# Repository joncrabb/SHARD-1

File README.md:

# SHARD-1
Code for the Surrey High Altitude Radiation Detector (SHARD-1)

Code written for 2 Arduino Nano controllers. 

To be used as payload with the Surrey EARS (Electronics and Amateur Radio Society) High Altitude Balloon Project

Go here to the EARS repositoryy containing PCB designs and code for the OBC: https://github.com/SurreyEARS/EARS-HAB

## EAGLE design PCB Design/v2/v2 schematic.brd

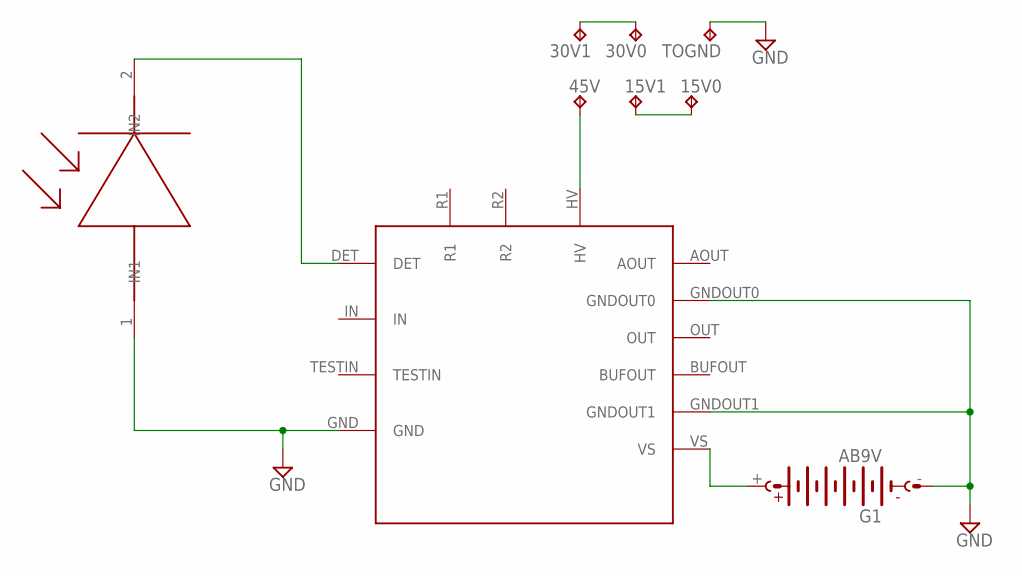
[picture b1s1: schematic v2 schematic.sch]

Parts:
15V0, 15V1, 30V0, 30V1, 45V: TP-063
G1: AB9V
PC21: A111
PINDIODE: S3590-08
TOGND: TP-063

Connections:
GND: G1.-, PC21.GND, PC21.GNDOUT0, PC21.GNDOUT1, PINDIODE.1 (IN1), TOGND.1
unnamed: 45V.1, PC21.HV
unnamed: 30V0.1, 30V1.1
unnamed: 15V0.1, 15V1.1
unnamed: G1.+, PC21.VS
unnamed: PC21.DET, PINDIODE.2 (IN2)

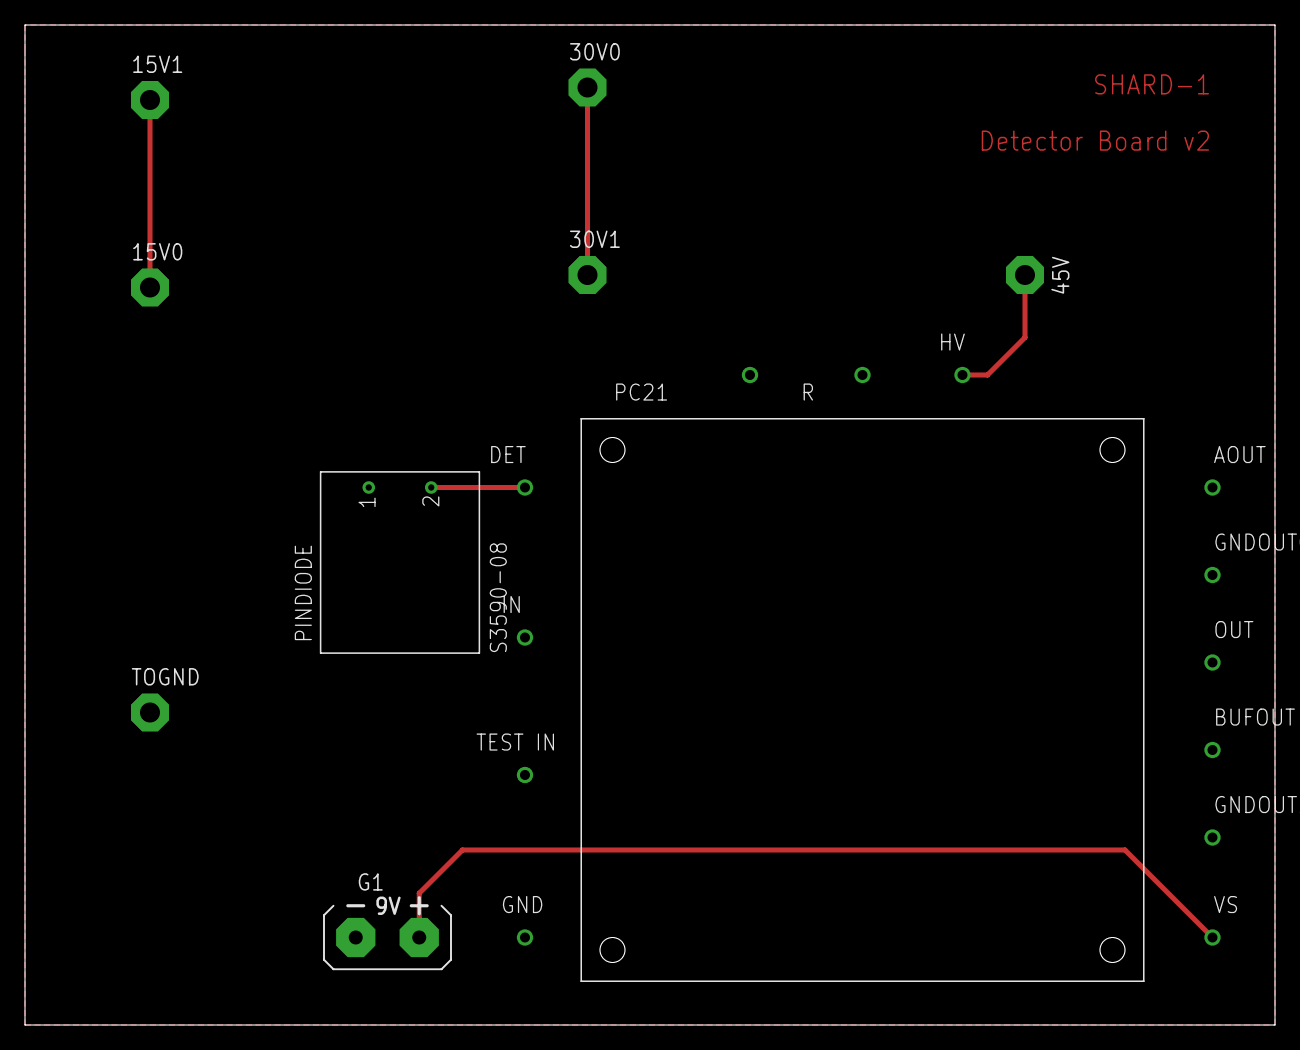
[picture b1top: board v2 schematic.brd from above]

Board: 2 copper layers, 100.0 x 80.0 mm, 9 parts (0 on the bottom side), 6 nets.

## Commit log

2015-04-24 Create README.md
    Initial creaton
2015-05-07 Slave code now works completely.
    Tested with Arduino Nano to read out the count through the serial port.
2015-05-07 Slave code now works, tested with an Arduino Nano.
2015-05-13 i2c now works fine.
2015-05-21 Master Code: Changed delay from 10s to 30s to reflect proper time resolution.
    Slave code: v1.1 (see version log for full details) added 'dataout' variable.
2015-05-27 Updated slave code: v1.2: It now disables the interrupts when reading the I2C is being used. This is so that the data can be taken off the device. However, this now adds some unwanted deadtime in the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
    Updated Master code so it reads every second (for testing)
2015-07-06 Updated Repository with PCB designs of the first version.
    Added slave code that flew on the EARS balloon.
2015-07-06 Added v2 design (unfinished)
2015-07-10 Added SHARD-1 Library
    Finalised v2 board for manufacturing.
2015-07-10 Updated pin connections for A111 Chip part
2015-07-19 Updated PCB design so diode is now reversed bias (correct)
2015-07-28 Updated design so the batteries now fit.
    Also discovered a problem with the battery clips having two holes!
    Fixed design for it now (have to drill holes separately)
2015-07-28 Final v2 design
2015-08-04 Create LICENCE
